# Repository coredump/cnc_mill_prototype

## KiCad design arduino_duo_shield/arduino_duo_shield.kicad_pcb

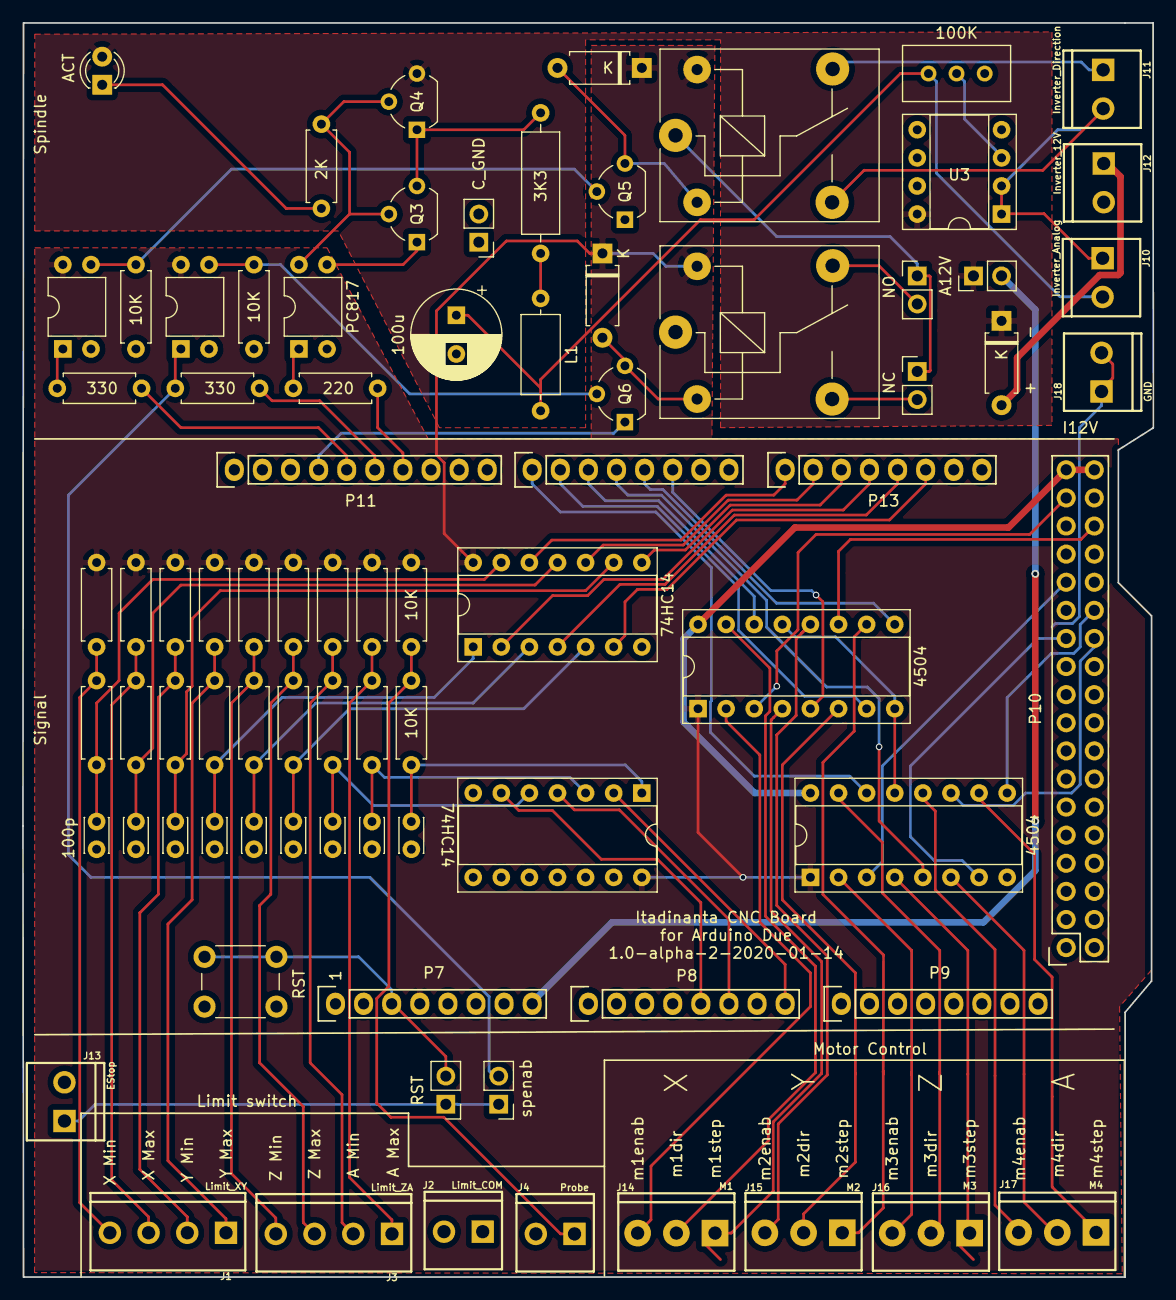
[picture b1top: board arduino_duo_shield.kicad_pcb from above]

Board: 2 copper layers, 102.2 x 113.3 mm, 82 parts (0 on the bottom side), 82 nets.

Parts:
C2, C3, C4, C5, C6, C7, C9, C10, C11: 100p; C_Disc_D3.0mm_W2.0mm_P2.50mm
C8: 100u; CP_Radial_D8.0mm_P3.50mm
D1: LED; LED_D3.0mm
D3, D4, D5: 1N4007; D_A-405_P7.62mm_Horizontal
J1: Limit_XY; SCREWTERMINAL-3.5MM-4
J2: Limit_COM; SCREWTERMINAL-3.5MM-2
J3: Limit_ZA; SCREWTERMINAL-3.5MM-4
J4: Probe; SCREWTERMINAL-3.5MM-2
J10: Inverter_Analog; SCREWTERMINAL-3.5MM-2
J11: Inverter_Direction; SCREWTERMINAL-3.5MM-2
J12: Inverter_12V; SCREWTERMINAL-3.5MM-2
J13: EStop; SCREWTERMINAL-3.5MM-2
J14: M1; SCREWTERMINAL-3.5MM-3
J15: M2; SCREWTERMINAL-3.5MM-3
J16: M3; SCREWTERMINAL-3.5MM-3
J17: M4; SCREWTERMINAL-3.5MM-3
J18: GND; SCREWTERMINAL-3.5MM-2
JP1, JP2, JP3, JP4: Jumper_NC_Small; PinHeader_1x02_P2.54mm_Vertical
JP5: EStop_RST; PinHeader_1x02_P2.54mm_Vertical
JP6: EStop_spenab; PinHeader_1x02_P2.54mm_Vertical
K2, K3: JQC-3F; Relay_SPDT_SANYOU_SRD_Series_Form_C
L1: 1m; L_Axial_L7.0mm_D3.3mm_P10.16mm_Horizontal_Fastron_MICC
P7: Power; Socket_Strip_Arduino_1x08
P8, P9: Analog; Socket_Strip_Arduino_1x08
P10: Digital; Socket_Strip_Arduino_2x18
P11: PWM; Socket_Strip_Arduino_1x10
P12: PWM; Socket_Strip_Arduino_1x08
P13: Communication; Socket_Strip_Arduino_1x08
Q3, Q5, Q6: 2N7000; TO-92_Wide
Q4: BS250; TO-92_Wide
R3, R4, R5, R6, R7, R8, R9, R10, R11, R12, R13, R14, R19, R20, R25, R26, R27, R28, R29, R30: 10K; R_Axial_DIN0207_L6.3mm_D2.5mm_P7.62mm_Horizontal
R15: 220; R_Axial_DIN0207_L6.3mm_D2.5mm_P7.62mm_Horizontal
R21: 2K; R_Axial_DIN0207_L6.3mm_D2.5mm_P7.62mm_Horizontal
R22, R24: 330; R_Axial_DIN0207_L6.3mm_D2.5mm_P7.62mm_Horizontal
R23: 3K3; R_Axial_DIN0309_L9.0mm_D3.2mm_P12.70mm_Horizontal
RV1: 100K; Potentiometer_Bourns_3296W_Vertical
SW1: SW_Push; SW_PUSH_6mm
U1, U2: 4504; DIP-16_W7.62mm_Socket
U3: LM358; DIP-8_W7.62mm_Socket
U4, U6: 74HC14; DIP-14_W7.62mm_Socket
U7, U8, U9: PC817; DIP-4_W7.62mm

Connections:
+3V3: D3.1, D4.1, K2.5, K3.5, P7.4, R3.2, R5.2, R7.2, R9.2, R11.2, R13.2, R19.2, R27.2, R29.2, U1.1, U2.1, U4.14, U6.14, U8.4, U9.4
+5V: P10.35, P10.36, U1.16, U2.16
/Debounce_x6/SWAmax+: J3.1, R27.1, R28.2
/Debounce_x6/SWAmin+: J3.2, R29.1, R30.2
/Debounce_x6/SWProbe+: J4.1, R19.1, R20.2
/Debounce_x6/SWXmax+: J1.3, R11.1, R12.2
/Debounce_x6/SWXmin+: J1.4, R13.1, R14.2
/Debounce_x6/SWYmax+: J1.1, R7.1, R8.2
/Debounce_x6/SWYmin+: J1.2, R9.1, R10.2
/Debounce_x6/SWZmax+: J3.3, R3.1, R4.2
/Debounce_x6/SWZmin+: J3.4, R5.1, R6.2
/Level_Shifter/hi_1_1: J14.3, U1.2
/Level_Shifter/hi_1_2: J14.2, U1.15
/Level_Shifter/hi_1_3: J14.1, U1.4
/Level_Shifter/hi_1_4: J15.3, U1.12
/Level_Shifter/hi_1_5: J15.2, U1.6
/Level_Shifter/hi_1_6: J15.1, U1.10
/Level_Shifter/hi_2_1: J16.3, U2.2
/Level_Shifter/hi_2_2: J16.2, U2.15
/Level_Shifter/hi_2_3: J16.1, U2.4
/Level_Shifter/hi_2_4: J17.3, U2.12
/Level_Shifter/hi_2_5: J17.2, U2.6
/Level_Shifter/hi_2_6: J17.1, U2.10
/Reset: JP5.2, P7.3, SW1.2
/Spindle_VFD_Control/I_PWRSAFE: D1.2, D5.1, JP4.1, Q4.3, U3.8
/Spindle_VFD_Control/ext_estop: JP6.2, R24.2, U9.1
/Spindle_VFD_Control/inverter_12V: D5.2, J12.1
/Spindle_VFD_Control/inverter_bw_switch: J11.2, K3.3
/Spindle_VFD_Control/inverter_frequency_10V: J10.1, U3.1, U3.2
/Spindle_VFD_Control/inverter_frequency_raw_10V: C8.1, J10.2, L1.2, RV1.1
/Spindle_VFD_Control/inverter_fw_switch: J11.1, K3.4
/Spindle_VFD_Control/inverter_gnd: C8.2, J12.2, JP1.1, K2.1, Q3.1, RV1.3, U3.4, U7.3
Amn: P8.5, U6.6
Amx: P8.6, U6.4
GND: C2.1, C3.1, C4.1, C5.1, C6.1, C7.1, C9.1, C10.1, C11.1, J2.1, J2.2, J4.2, J13.2, J18.1, J18.2, JP1.2, P7.6, P7.7, P10.1, P10.2, P11.4, Q5.1, Q6.1, R25.2, R26.2, SW1.1, U1.8, U1.13, U2.8, U2.13, U4.7, U6.7, U7.2, U8.2, U9.2
unnamed: C2.2, R4.1, U4.5
unnamed: C3.2, R6.1, U4.3
unnamed: C4.2, R8.1, U4.1
unnamed: C5.2, R10.1, U4.9
unnamed: C6.2, R12.1, U4.11
unnamed: C7.2, R14.1, U4.13
unnamed: C9.2, R20.1, U6.1
unnamed: C10.2, R28.1, U6.3
unnamed: C11.2, R30.1, U6.5
unnamed: D1.1, R21.1
unnamed: D3.2, K3.2, Q5.3
unnamed: D4.2, K2.2, Q6.3
unnamed: J13.1, JP5.1, JP6.1
unnamed: JP2.1, JP3.1, K3.1
unnamed: JP2.2, K2.3
unnamed: JP3.2, K2.4
unnamed: L1.1, R23.2
unnamed: Q3.2, Q4.2, R21.2, U7.4
unnamed: Q3.3, Q4.1, R23.1
unnamed: Q5.2, R25.1, U8.3
unnamed: Q6.2, R26.1, U9.3
unnamed: R15.2, U7.1
unnamed: R22.2, U8.1
unnamed: RV1.2, U3.3
Probe: P8.8, U6.2
Xmn: P13.1, U4.12
Xmx: P13.2, U4.10
Ymn: P13.3, U4.8
Ymx: P13.4, U4.2
Zmn: P13.5, U4.4
Zmx: P13.6, U4.6
ext_12v: JP4.2, P7.8
m1dir: P12.3, U1.14
m1enab: P10.33, U1.3
m1step: P12.6, U1.5
m2dir: P12.2, U1.7
m2enab: P10.32, U1.11
m2step: P12.5, U1.9
m3dir: P12.1, U2.14
m3enab: P10.27, U2.3
m3step: P12.4, U2.5
m4dir: P10.23, U2.7
m4enab: P10.24, U2.11
m4step: P10.26, U2.9
spdir: P11.5, R22.1
spenab: P11.6, R24.1
sppwm: P11.7, R15.1

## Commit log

2020-01-24 Added screw connectors to everything
